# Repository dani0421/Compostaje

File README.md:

# Proyecto de Sistemas embebidos
Este es el repositorio del proyecto (Nombre del proyecto) de la materia de Sitemas embebidos 

## Integrantes
Daniela Valentina Amaya Vargas

Diana Patricia Cortés Nava

Julian David Escobar Jamioy

## Problemática
Cada año la cantidad de residuos organicos a nivel mundial es de 11.200 millones y contribuyen un 5% a las emisiones de gases de efecto invernadero [1], esto cada año incrementa el calentamiento global, sin contar con que poco a poco los basureros alrededor del mundo estan llegando a su maxima capacidad de desechos. La mayoria de estos residuos se generan en los hogares y generalmente no son reutilizados, es por esto que nace la idea de crear (nombre del proyecto), una basurera de desechos organicos capaz de convertir los residuos en compostaje, esto permitirá que se logren reducir las emisiones de gases de efecto invernadero reutilizando los residuos organicos y convirtiendolos en tierra para abonar las plantas del hogar e incluso las plantas de una huerta.

## Objetivos
### Objetivo General:
Desarrollar un sistema embebido que permita darle un manejo óptimo a los desechos organicos de manera cómoda y sencilla, con el fin de poder ser implementado por cualquier usuario de manera doméstica. 
### Objetivos Especificos:
* Diseñar un sistema compacto que integre diseño de PCB, programación de microcontroladores como ESP32 y diseño físico del prototipo.
* Obtener un producto final comercial, en el que se tenga en cuenta también aspectos financieros incluyendo mano de obra.
* Documentar todas las etapas del proceso de creación del proyecto hasta su finalización.

## Alcance
Elaborar un (nombre del proyecto) capaz de transformar, en cada uso, un volumen no mayor a 1.76 L de residuos orgánicos en compostaje. Contará con 3 modos de acuerdo a cuan lleno se encuentre el tambor, los cuales podrán ser elegidos según usuario vea conveniente; una vez elegido un modo, la pantalla OLED indicará la temperatura, humedad y el tiempo que aun haga falta para que el compostaje esté listo y pueda ser retirado de (nombre del proyecto). 

## Requerimientos

### Requerimientos funcionales

* Seleccionar el nivel de compostaje que el dispositivo contiene.
* Visualizar por medio de pantalla el tiempo que falta para finalizar el proceso.
* Notificar al usuario cuando los filtros requieran ser reemplazados. 
* Evitar que el dispositivo genere malos olores.
* Notificar al usuario por medio de un mensaje vía Telegram cuando se acabó el proceso de compostaje.

### Requerimientos no funcionales

* El sistema requiere de un tiempo mínimo de 24 horas para realizar un proceso.

## Diagrama de bloques

## Componentes

### Optoacoplador
Servira para realizar un desacople fisico entre el ESP32 y el controlador (LN298N) de nuestros motores, debido a que su voltaje de trabajo es diferente; se hara uso de la referencia TLP281 de 4 canales.

### Controlador de Motor
Referencia L298N que posee 4 pines de salida, teniendo en cuenta que nuestro motor es un KH56JM2U047 de bifase y con 4 pines de entrada.

### Pantalla OLED
Se usará la referencia SSD1306, la cual posee una matriz de 128x64 y cuya alimentación necesaaria es de 3.3V ([DATASHEET](https://html.alldatasheet.com/html-pdf/1179026/ETC2/SSD1306/701/6/SSD1306.html)); donde el usuario podra observar el tiempo que aun hace falta para que el compostaje este listo. Cuya dirección para I2C es 0x3C.

El SDA se conecta al pin 33 del ESP32 y el SCL al pin 36 de ESP32, cabe resaltar que en la placa no quedaran orificios para la pantalla, unicamente los pines para hacer la conexión.

### Touch
Aunque la ESP posee pines que se pueden usar como touch, se optó por hacer uso de un touch capacitivo externo, el cual nos permitirá abrir la tapa principal, que es por donde se introducira los residuos organicos junto a la tierra que posteriormente se mezclará. La referencia a usar es HW-139

### Motor Nema
Para el proceso de triturado de los residuos organicos y mezclado se usaran dos motores NEMA 17, estos son motores bipolares que pueden ser alimentados con un voltaje de 12 a 24 voltios, se opto por alimentarlos a un voltaje de 12V. 

### Servomotor

El servomotor se usara para abrir y cerrar la tapa de la basuera 

## Diseno PCB
A continuacion se muestra el diseno que se realizo para la PCB

## Montaje fisico
Para el montaje fisico se imprimeron en 3D las siguientes piezas:

Luego se procedio al armado de el prototipo como se muestra en las siguientes imagenes:

https://user-images.githubusercontent.com/92388558/206091587-dc1af1c8-e01d-440c-9be7-15e96c51869d.mp4

## Pruebas de funcionamiento

https://user-images.githubusercontent.com/103794195/206186310-e058958a-483b-43ef-9478-b426c58254a1.mp4

## Referencias
[1] Nations, U. (2022). Datos y cifras | Naciones Unidas. Retrieved 24 August 2022, from https://www.un.org/es/actnow/facts-and-figures

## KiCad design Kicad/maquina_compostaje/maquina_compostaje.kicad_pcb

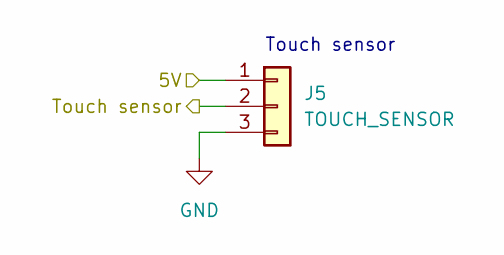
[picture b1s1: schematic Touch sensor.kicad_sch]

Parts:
J5: TOUCH_SENSOR; JST_EH_B3B-EH-A_1x03_P2.50mm_Vertical

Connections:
5V: J5.1; also elsewhere on the board
GND: J5.3; also elsewhere on the board
Touch_sensor: J5.2; also elsewhere on the board

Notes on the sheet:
Touch sensor

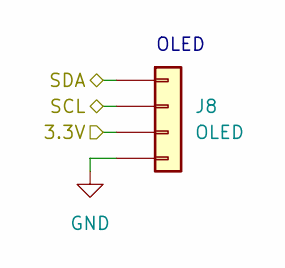
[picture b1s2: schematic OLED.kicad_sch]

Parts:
J8: OLED; JST_EH_B4B-EH-A_1x04_P2.50mm_Vertical

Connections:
3.3V: J8.3; also elsewhere on the board
GND: J8.4; also elsewhere on the board
SCL: J8.2; also elsewhere on the board
SDA: J8.1; also elsewhere on the board

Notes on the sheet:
OLED

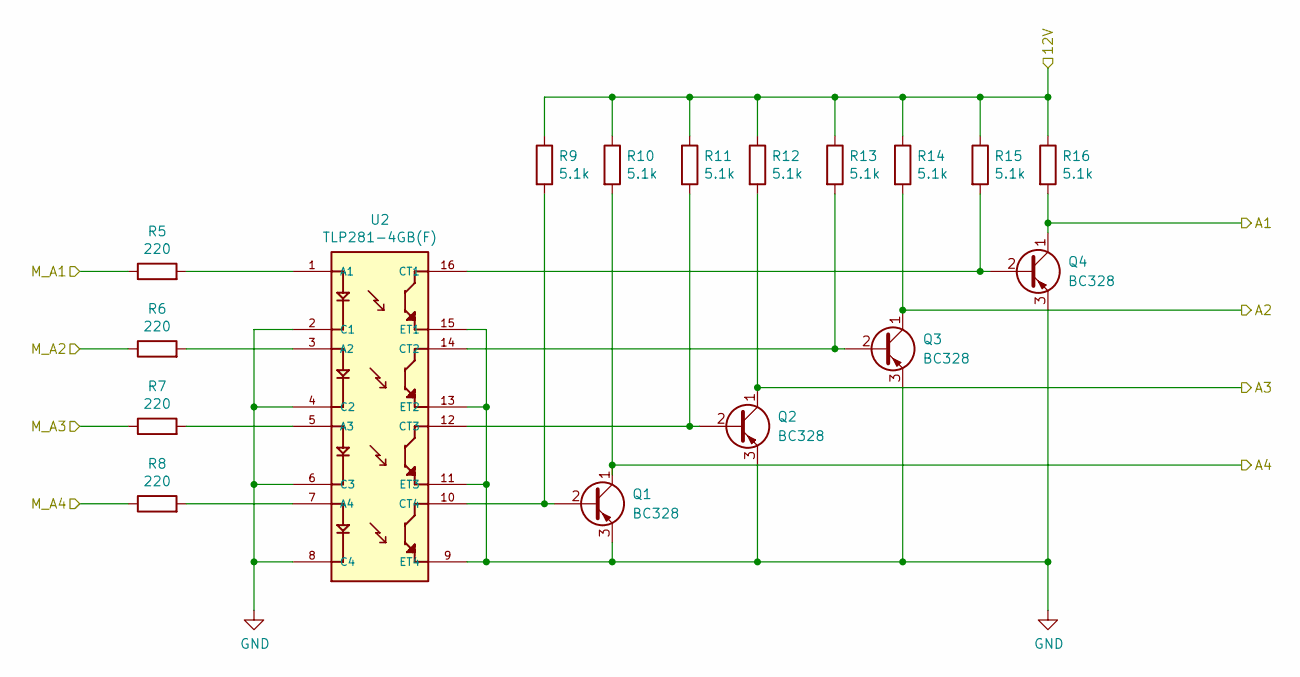
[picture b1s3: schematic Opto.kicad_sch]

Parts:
Q1, Q2, Q3, Q4: BC328; SOT-23
R5, R6, R7, R8: 220; R_1206_3216Metric_Pad1.30x1.75mm_HandSolder
R9, R10, R11, R12, R13, R14, R15, R16: 5.1k; R_1206_3216Metric_Pad1.30x1.75mm_HandSolder
U2: TLP281-4GB(F); SO-16_5.3x10.2mm_P1.27mm

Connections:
12V: R9.1, R10.1, R11.1, R12.1, R13.1, R14.1, R15.1, R16.1; also elsewhere on the board
/Motor A/IN 1A: Q4.1 (C), R16.2; also elsewhere on the board
/Motor A/IN 2A: Q3.1 (C), R14.2; also elsewhere on the board
/Motor A/IN 3A: Q2.1 (C), R12.2; also elsewhere on the board
/Motor A/IN 4A: Q1.1 (C), R10.2; also elsewhere on the board
GND: Q1.3 (E), Q2.3 (E), Q3.3 (E), Q4.3 (E), U2.2 (C1), U2.4 (C2), U2.6 (C3), U2.8 (C4), U2.9 (ET4), U2.11 (ET3), U2.13 (ET2), U2.15 (ET1); also elsewhere on the board
M_A1: R5.1; also elsewhere on the board
M_A2: R6.1; also elsewhere on the board
M_A3: R7.1; also elsewhere on the board
M_A4: R8.1; also elsewhere on the board
unnamed: Q1.2 (B), R9.2, U2.10 (CT4)
unnamed: Q2.2 (B), R11.2, U2.12 (CT3)
unnamed: Q3.2 (B), R13.2, U2.14 (CT2)
unnamed: Q4.2 (B), R15.2, U2.16 (CT1)
unnamed: R5.2, U2.1 (A1)
unnamed: R6.2, U2.3 (A2)
unnamed: R7.2, U2.5 (A3)
unnamed: R8.2, U2.7 (A4)

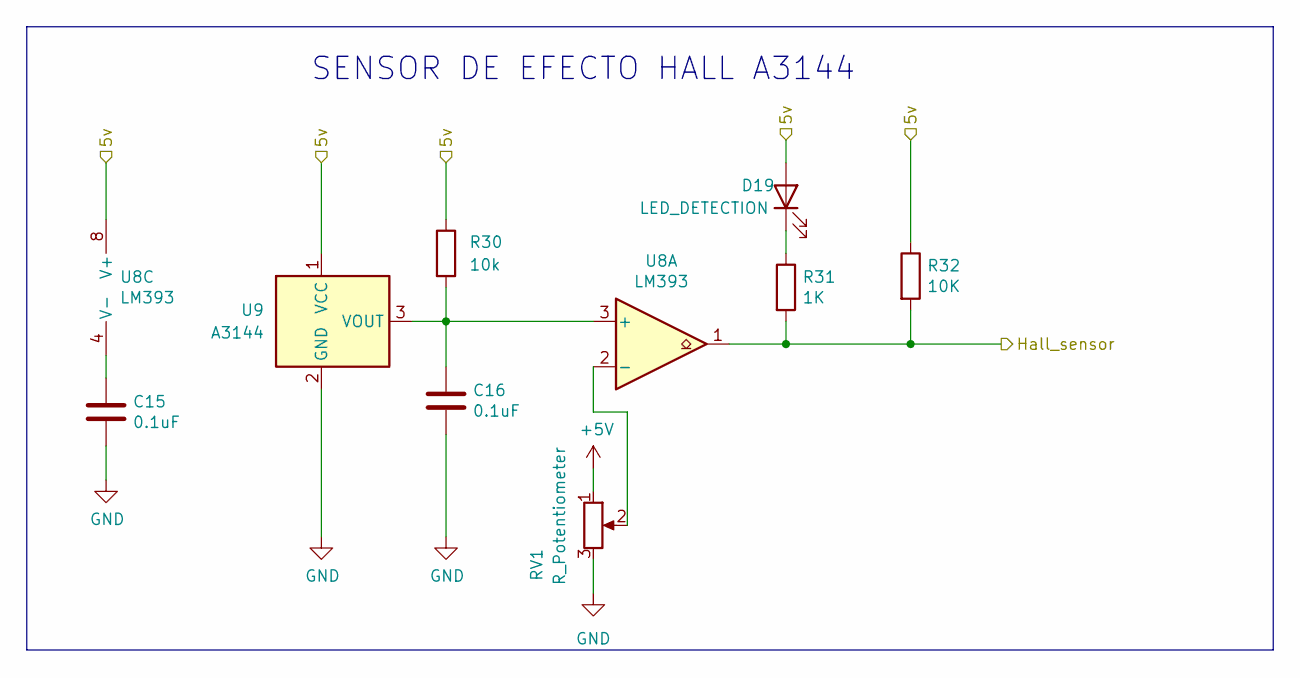
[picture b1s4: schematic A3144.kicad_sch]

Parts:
C15, C16: 0.1uF; C_1206_3216Metric_Pad1.33x1.80mm_HandSolder
D19: LED_DETECTION; LED_1206_3216Metric_Pad1.42x1.75mm_HandSolder
R30: 10k; R_1206_3216Metric_Pad1.30x1.75mm_HandSolder
R31: 1K; R_1206_3216Metric_Pad1.30x1.75mm_HandSolder
R32: 10K; R_1206_3216Metric_Pad1.30x1.75mm_HandSolder
RV1: R_Potentiometer; Potentiometer_ACP_CA6-VSMD_Vertical
U8: LM393; SOIC-8_3.9x4.9mm_P1.27mm
U9: A3144; Allegro_SIP-3

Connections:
5V: D19.2 (A), R30.1, R32.1, RV1.1, U8.8 (V+), U9.1 (VCC); also elsewhere on the board
GND: C15.2, C16.2, RV1.3, U9.2 (GND); also elsewhere on the board
Hall_sensor: R31.2, R32.2, U8.1; also elsewhere on the board
unnamed: C15.1, U8.4 (V-)
unnamed: C16.1, R30.2, U8.3 (+), U9.3 (VOUT)
unnamed: D19.1 (K), R31.1
unnamed: RV1.2, U8.2 (-)

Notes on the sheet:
SENSOR DE EFECTO HALL A3144

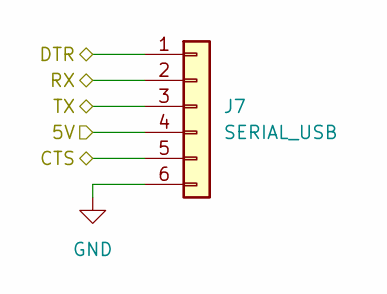
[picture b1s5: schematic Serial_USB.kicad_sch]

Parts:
J7: SERIAL_USB; JST_EH_B6B-EH-A_1x06_P2.50mm_Vertical

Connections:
5V: J7.4; also elsewhere on the board
/Serial_USB/CTS: J7.5
/Serial_USB/DTR: J7.1
GND: J7.6; also elsewhere on the board
RX: J7.2; also elsewhere on the board
TX: J7.3; also elsewhere on the board

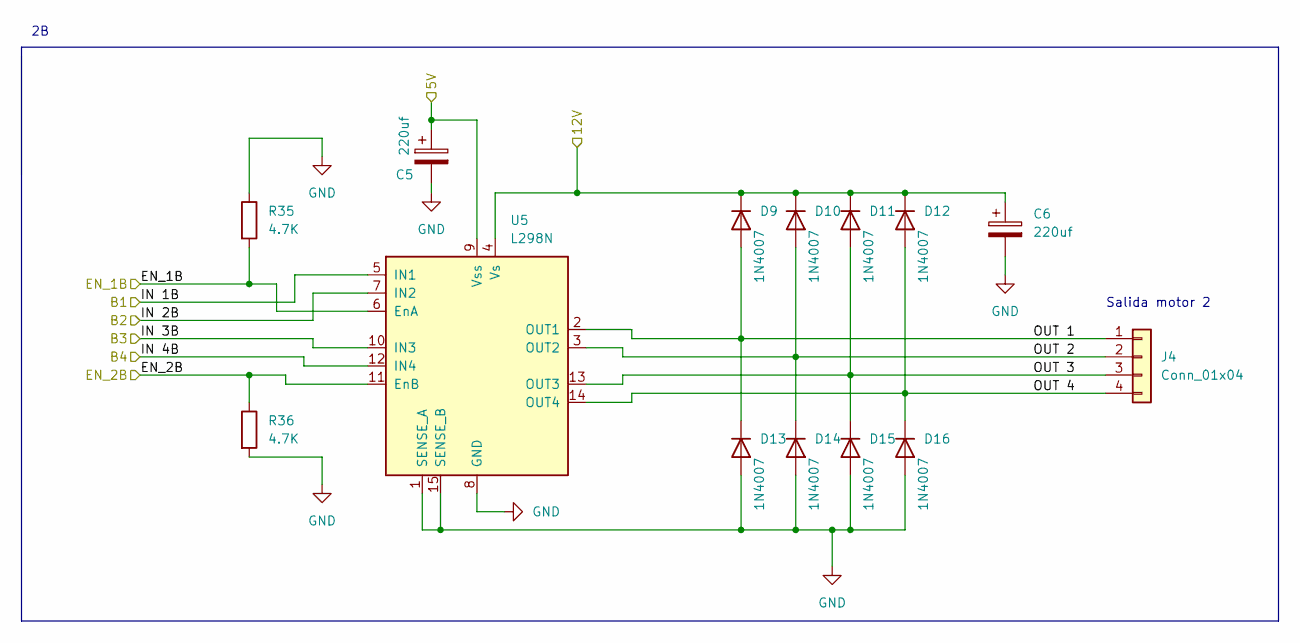
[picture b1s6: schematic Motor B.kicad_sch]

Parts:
C5, C6: 220uf; CP_Elec_8x10
D9, D10, D11, D12, D13, D14, D15, D16: 1N4007; D_SOD-128
J4: Conn_01x04; JST_EH_B4B-EH-A_1x04_P2.50mm_Vertical
R35, R36: 4.7K; R_1206_3216Metric_Pad1.30x1.75mm_HandSolder
U5: L298N; TO-220-15_P2.54x2.54mm_StaggerOdd_Lead4.58mm_Vertical

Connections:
5V: C5.1, U5.9 (Vss); also elsewhere on the board
12V: C6.1, D9.1 (K), D10.1 (K), D11.1 (K), D12.1 (K), U5.4 (Vs); also elsewhere on the board
/Motor B/IN 1B: U5.5 (IN1); also elsewhere on the board
/Motor B/IN 2B: U5.7 (IN2); also elsewhere on the board
/Motor B/IN 3B: U5.10 (IN3); also elsewhere on the board
/Motor B/IN 4B: U5.12 (IN4); also elsewhere on the board
/Motor B/OUT 1: D9.2 (A), D13.1 (K), J4.1, U5.2 (OUT1)
/Motor B/OUT 2: D10.2 (A), D14.1 (K), J4.2, U5.3 (OUT2)
/Motor B/OUT 3: D11.2 (A), D15.1 (K), J4.3, U5.13 (OUT3)
/Motor B/OUT 4: D12.2 (A), D16.1 (K), J4.4, U5.14 (OUT4)
EN_1B: R35.2, U5.6 (EnA); also elsewhere on the board
EN_2B: R36.1, U5.11 (EnB); also elsewhere on the board
GND: C5.2, C6.2, D13.2 (A), D14.2 (A), D15.2 (A), D16.2 (A), R35.1, R36.2, U5.1 (SENSE_A), U5.8 (GND), U5.15 (SENSE_B); also elsewhere on the board

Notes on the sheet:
Salida motor 2

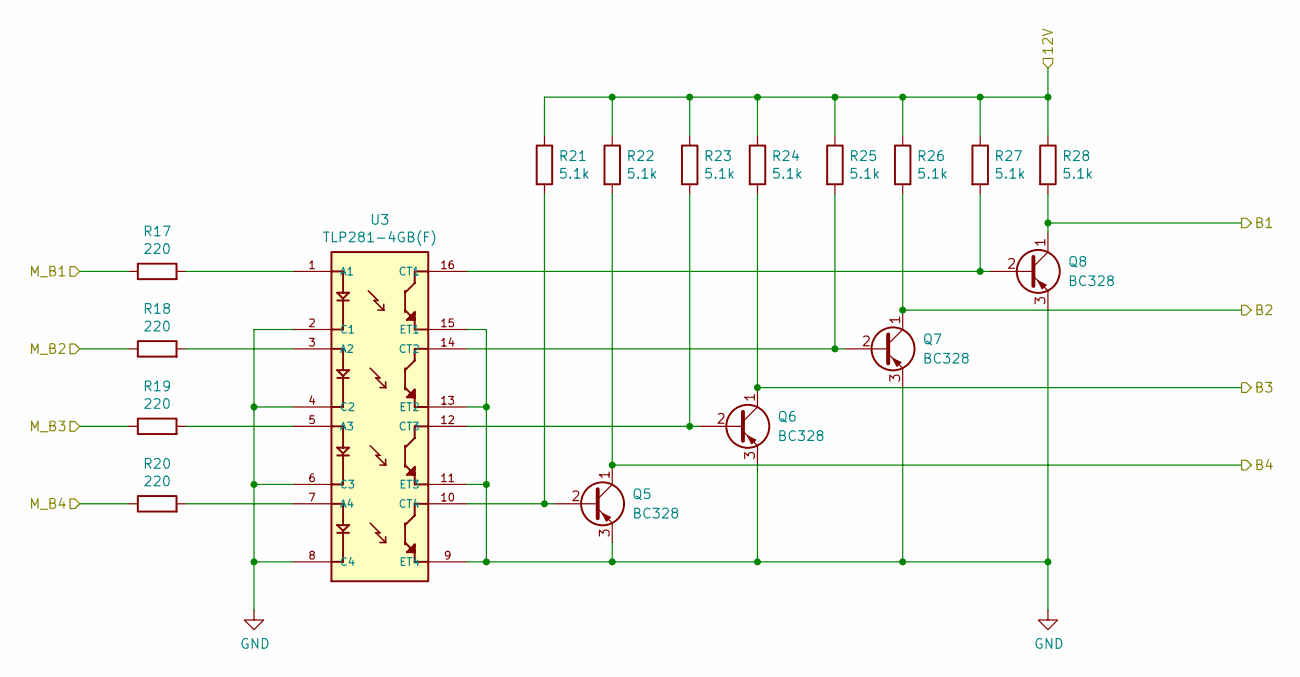
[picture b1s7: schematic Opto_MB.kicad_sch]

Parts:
Q5, Q6, Q7, Q8: BC328; SOT-23
R17, R18, R19, R20: 220; R_1206_3216Metric_Pad1.30x1.75mm_HandSolder
R21, R22, R23, R24, R25, R26, R27, R28: 5.1k; R_1206_3216Metric_Pad1.30x1.75mm_HandSolder
U3: TLP281-4GB(F); SO-16_5.3x10.2mm_P1.27mm

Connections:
12V: R21.1, R22.1, R23.1, R24.1, R25.1, R26.1, R27.1, R28.1; also elsewhere on the board
/Motor B/IN 1B: Q8.1 (C), R28.2; also elsewhere on the board
/Motor B/IN 2B: Q7.1 (C), R26.2; also elsewhere on the board
/Motor B/IN 3B: Q6.1 (C), R24.2; also elsewhere on the board
/Motor B/IN 4B: Q5.1 (C), R22.2; also elsewhere on the board
GND: Q5.3 (E), Q6.3 (E), Q7.3 (E), Q8.3 (E), U3.2 (C1), U3.4 (C2), U3.6 (C3), U3.8 (C4), U3.9 (ET4), U3.11 (ET3), U3.13 (ET2), U3.15 (ET1); also elsewhere on the board
M_B1: R17.1; also elsewhere on the board
M_B2: R18.1; also elsewhere on the board
M_B3: R19.1; also elsewhere on the board
M_B4: R20.1; also elsewhere on the board
unnamed: Q5.2 (B), R21.2, U3.10 (CT4)
unnamed: Q6.2 (B), R23.2, U3.12 (CT3)
unnamed: Q7.2 (B), R25.2, U3.14 (CT2)
unnamed: Q8.2 (B), R27.2, U3.16 (CT1)
unnamed: R17.2, U3.1 (A1)
unnamed: R18.2, U3.3 (A2)
unnamed: R19.2, U3.5 (A3)
unnamed: R20.2, U3.7 (A4)

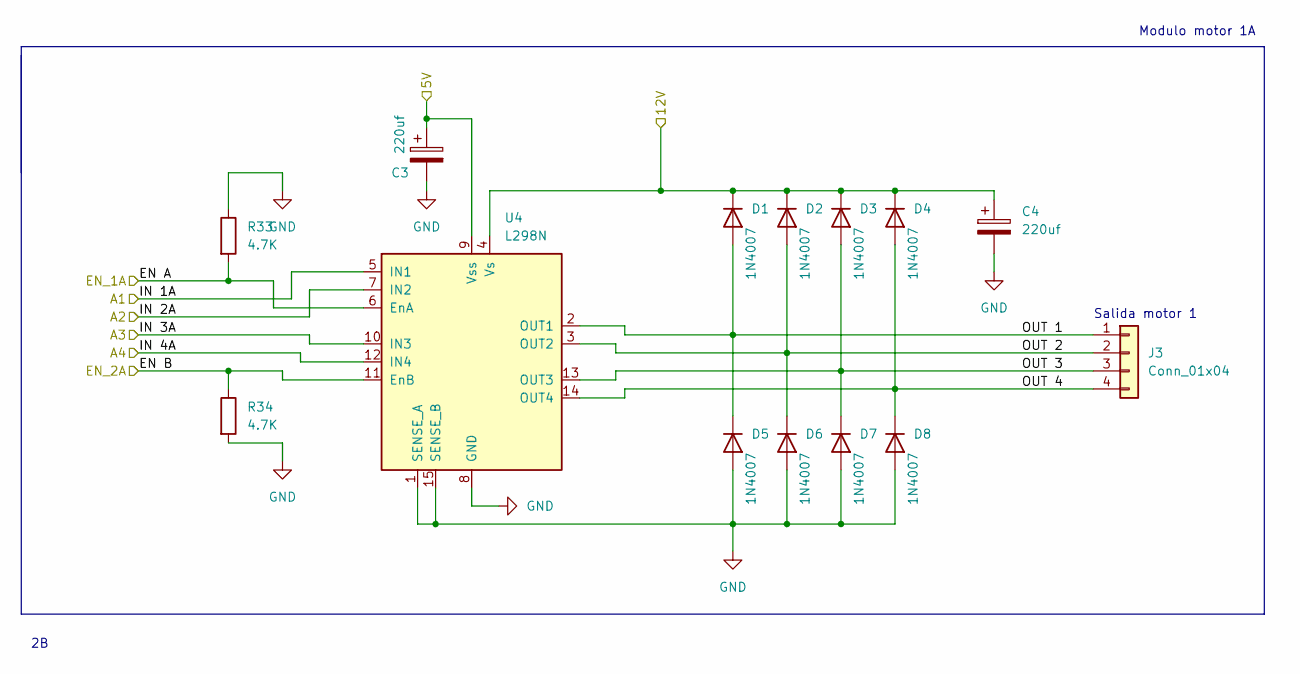
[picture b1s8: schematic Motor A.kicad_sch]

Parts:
C3, C4: 220uf; CP_Elec_8x10
D1, D2, D3, D4, D5, D6, D7, D8: 1N4007; D_SOD-128
J3: Conn_01x04; JST_EH_B4B-EH-A_1x04_P2.50mm_Vertical
R33, R34: 4.7K; R_1206_3216Metric_Pad1.30x1.75mm_HandSolder
U4: L298N; TO-220-15_P2.54x2.54mm_StaggerOdd_Lead4.58mm_Vertical

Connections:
5V: C3.1, U4.9 (Vss); also elsewhere on the board
12V: C4.1, D1.1 (K), D2.1 (K), D3.1 (K), D4.1 (K), U4.4 (Vs); also elsewhere on the board
/Motor A/IN 1A: U4.5 (IN1); also elsewhere on the board
/Motor A/IN 2A: U4.7 (IN2); also elsewhere on the board
/Motor A/IN 3A: U4.10 (IN3); also elsewhere on the board
/Motor A/IN 4A: U4.12 (IN4); also elsewhere on the board
/Motor A/OUT 1: D1.2 (A), D5.1 (K), J3.1, U4.2 (OUT1)
/Motor A/OUT 2: D2.2 (A), D6.1 (K), J3.2, U4.3 (OUT2)
/Motor A/OUT 3: D3.2 (A), D7.1 (K), J3.3, U4.13 (OUT3)
/Motor A/OUT 4: D4.2 (A), D8.1 (K), J3.4, U4.14 (OUT4)
EN_1A: R33.2, U4.6 (EnA); also elsewhere on the board
EN_2A: R34.1, U4.11 (EnB); also elsewhere on the board
GND: C3.2, C4.2, D5.2 (A), D6.2 (A), D7.2 (A), D8.2 (A), R33.1, R34.2, U4.1 (SENSE_A), U4.8 (GND), U4.15 (SENSE_B); also elsewhere on the board

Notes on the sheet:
Modulo motor 1A
Salida motor 1

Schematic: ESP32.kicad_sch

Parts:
C1: 10uf; C_1206_3216Metric_Pad1.33x1.80mm_HandSolder
C2: 10uf; C_1206_3216Metric
C17: 0.1uF; C_1206_3216Metric_Pad1.33x1.80mm_HandSolder
C18: 10uF; C_1206_3216Metric_Pad1.33x1.80mm_HandSolder
J1: OTHERS; JST_EH_B6B-EH-A_1x06_P2.50mm_Vertical
J2: GPIO; JST_EH_B5B-EH-A_1x05_P2.50mm_Vertical
R1, R4: 10k; R_1206_3216Metric_Pad1.30x1.75mm_HandSolder
R2, R3: 4.7K; R_1206_3216Metric_Pad1.30x1.75mm_HandSolder
SW1: RESET; smd_push2
SW2: BOOT; smd_push2
U1: ESP32-WROOM-32

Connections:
3.3V: C17.2, C18.1, R1.1, R4.1, U1.2 (VDD); also elsewhere on the board
+3.3V: R2.2, R3.2
/ESP32/SCK: J1.2, U1.20 (SCK/CLK)
/ESP32/SCS: J1.1, U1.19 (SCS/CMD)
/ESP32/SD0: J1.6, U1.21 (SDO/SD0)
/ESP32/SD1: J1.5, U1.22 (SDI/SD1)
/ESP32/SD2: J1.4, U1.17 (SHD/SD2)
/ESP32/SD3: J1.3, U1.18 (SWP/SD3)
/ESP32/gpio2: J2.1, U1.24 (IO2)
/ESP32/gpio16: J2.2, U1.27 (IO16)
/ESP32/gpio17: J2.3, U1.28 (IO17)
/ESP32/gpio23: J2.4, U1.37 (IO23)
/ESP32/gpio35: J2.5, U1.7 (IO35)
EN_1A: U1.26 (IO4); also elsewhere on the board
EN_1B: U1.9 (IO33); also elsewhere on the board
EN_2A: U1.29 (IO5); also elsewhere on the board
EN_2B: U1.6 (IO34); also elsewhere on the board
GND: C1.2, C2.2, C17.1, C18.2, SW1.1, SW1.2, SW2.1, SW2.2, U1.1 (GND), U1.15 (GND), U1.38 (GND), U1.39 (GND); also elsewhere on the board
Hall_sensor: U1.31 (IO19); also elsewhere on the board
M_A1: U1.14 (IO12); also elsewhere on the board
M_A2: U1.16 (IO13); also elsewhere on the board
M_A3: U1.13 (IO14); also elsewhere on the board
M_A4: U1.23 (IO15); also elsewhere on the board
M_B1: U1.10 (IO25); also elsewhere on the board
M_B2: U1.11 (IO26); also elsewhere on the board
M_B3: U1.12 (IO27); also elsewhere on the board
M_B4: U1.8 (IO32); also elsewhere on the board
unnamed: C1.1, R1.2, SW1.3, SW1.4, U1.3 (EN)
unnamed: C2.1, R4.2, SW2.3, SW2.4, U1.25 (IO0)
RX: U1.35 (TXD0/IO1); also elsewhere on the board
SCL: R2.1, U1.36 (IO22); also elsewhere on the board
SDA: R3.1, U1.33 (IO21); also elsewhere on the board
TX: U1.34 (RXD0/IO3); also elsewhere on the board
Touch_sensor: U1.30 (IO18); also elsewhere on the board

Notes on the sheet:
gpio MA 12,13,14,15 MB 25,26,27,32 para motores SDA y SCL van a OLED gpio18 touch sensor gpio19 sensor de efecto hall

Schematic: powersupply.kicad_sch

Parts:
C7, C10, C11, C14: 10uf; C_1206_3216Metric_Pad1.33x1.80mm_HandSolder
C8, C12: 10uf; CP_Elec_6.3x5.4
C9, C13: 100nf; C_1206_3216Metric_Pad1.33x1.80mm_HandSolder
D17: 1N4002; D_SOD-128
D18: LED; LED_1206_3216Metric_Pad1.42x1.75mm_HandSolder
F1: 1A; Fuse_1206_3216Metric_Pad1.42x1.75mm_HandSolder
F2: 2A; Fuse_1206_3216Metric_Pad1.42x1.75mm_HandSolder
J6: Barrel_Jack_MountingPin; BarrelJack_Horizontal
R29: 1k; R_1206_3216Metric_Pad1.30x1.75mm_HandSolder
U6: AMS1117-5.0; SOT-223; PARTREV N/A
U7: AMS1117-3.3; SOT-223; PARTREV NA

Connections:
3.3V: C12.1, C13.1, C14.1, U7.2 (VOUT); also elsewhere on the board
5V: C8.1, C9.1, C10.1, C11.1, D18.2 (A), U6.2 (VOUT), U7.3 (VIN); also elsewhere on the board
12V: F2.2; also elsewhere on the board
GND: C7.2, C8.2, C9.2, C10.2, C11.2, C12.2, C13.2, C14.2, J6.2, J6.MP (MountPin), R29.2, U6.1 (GND/ADJ), U7.1 (ADJ/GND); also elsewhere on the board
unnamed: C7.1, F1.2, U6.3 (VIN)
unnamed: D17.1 (K), F1.1, F2.1
unnamed: D17.2 (A), J6.1
unnamed: D18.1 (K), R29.1

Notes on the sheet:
Led de energizacion
Regulador de 5V - 1A
Regulador de 3.3V - 1A

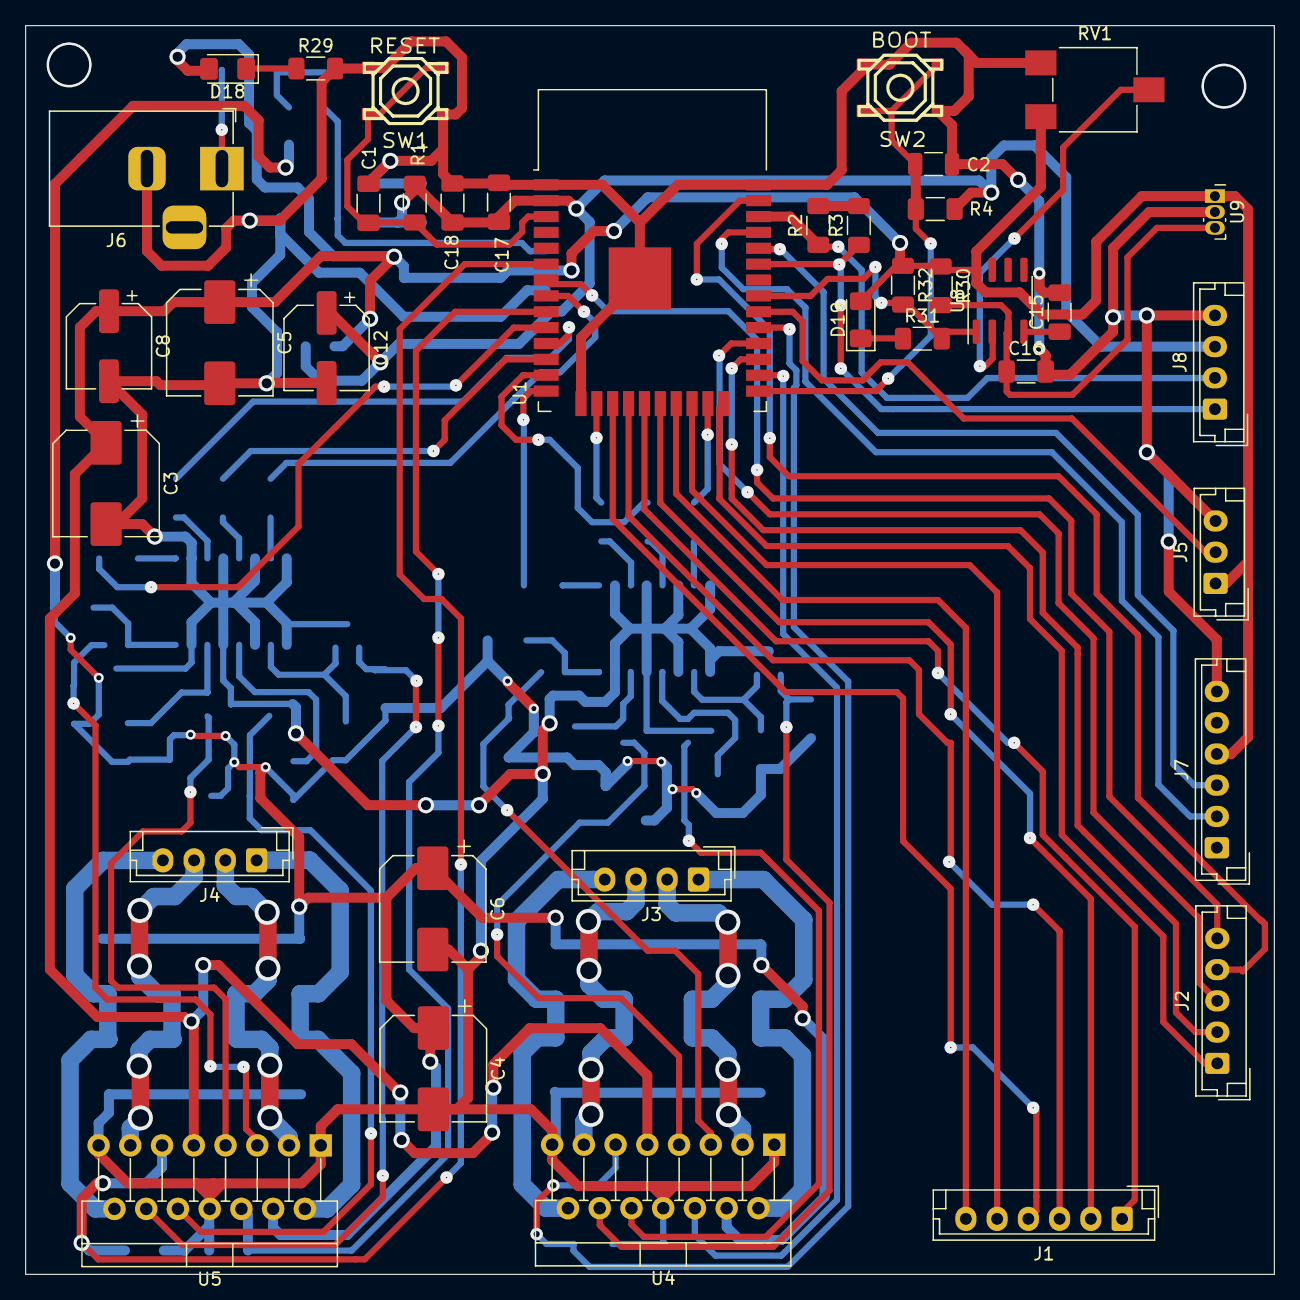
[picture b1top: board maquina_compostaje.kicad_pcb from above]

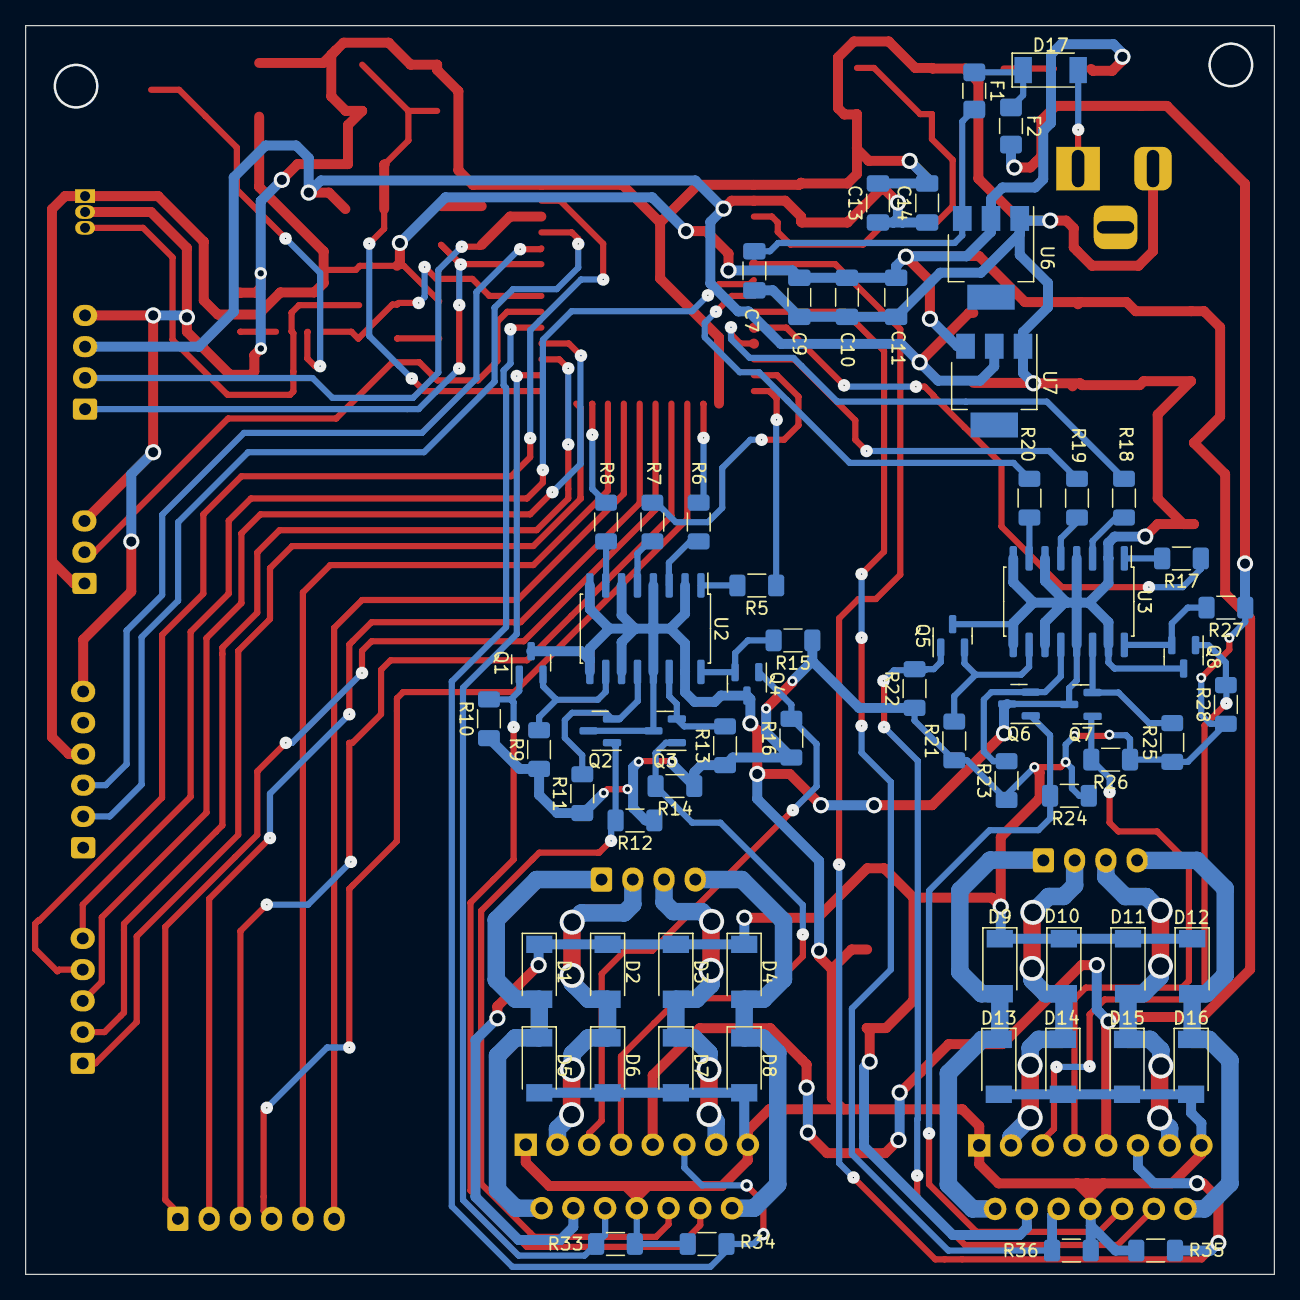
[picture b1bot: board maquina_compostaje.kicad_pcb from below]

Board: 2 copper layers, 99.9 x 99.9 mm, 103 parts (65 on the bottom side), 76 nets.

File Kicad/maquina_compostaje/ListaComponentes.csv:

"Id";"Designator";"Package";"Quantity";"Designation";"Supplier and ref";
1;"C18";"C_1206_3216Metric_Pad1.33x1.80mm_HandSolder";1;"10uF";;;
2;"SW2";"smd_push2";1;"BOOT";;;
3;"C17,C15,C16";"C_1206_3216Metric_Pad1.33x1.80mm_HandSolder";3;"0.1uF";;;
4;"R3,R2,R36,R34,R35,R33";"R_1206_3216Metric_Pad1.30x1.75mm_HandSolder";6;"4.7K";;;
5;"C4,C5,C6,C3";"CP_Elec_8x10";4;"220uf";;;
6;"J2";"JST_EH_B5B-EH-A_1x05_P2.50mm_Vertical";1;"GPIO";;;
7;"SW1";"smd_push2";1;"RESET";;;
8;"J5";"JST_EH_B3B-EH-A_1x03_P2.50mm_Vertical";1;"TOUCH_SENSOR";;;
9;"R4,R30,R1";"R_1206_3216Metric_Pad1.30x1.75mm_HandSolder";3;"10k";;;
10;"D18";"LED_1206_3216Metric_Pad1.42x1.75mm_HandSolder";1;"LED";;;
11;"U9";"Allegro_SIP-3";1;"A3144";;;
12;"RV1";"Potentiometer_ACP_CA6-VSMD_Vertical";1;"R_Potentiometer";;;
13;"J8";"JST_EH_B4B-EH-A_1x04_P2.50mm_Vertical";1;"OLED";;;
14;"U8";"SOIC-8_3.9x4.9mm_P1.27mm";1;"LM393";;;
15;"U5,U4";"TO-220-15_P2.54x2.54mm_StaggerOdd_Lead4.58mm_Vertical";2;"L298N";;;
16;"C2";"C_1206_3216Metric";1;"10uf";;;
17;"R32";"R_1206_3216Metric_Pad1.30x1.75mm_HandSolder";1;"10K";;;
18;"U1";"ESP32-WROOM-32";1;"ESP32-WROOM-32";;;
19;"D19";"LED_1206_3216Metric_Pad1.42x1.75mm_HandSolder";1;"LED_DETECTION";;;
20;"J7";"JST_EH_B6B-EH-A_1x06_P2.50mm_Vertical";1;"SERIAL_USB";;;
21;"C8,C12";"CP_Elec_6.3x5.4";2;"10uf";;;
22;"J1";"JST_EH_B6B-EH-A_1x06_P2.50mm_Vertical";1;"OTHERS";;;
23;"J3,J4";"JST_EH_B4B-EH-A_1x04_P2.50mm_Vertical";2;"Conn_01x04";;;
24;"R31";"R_1206_3216Metric_Pad1.30x1.75mm_HandSolder";1;"1K";;;
25;"J6";"BarrelJack_Horizontal";1;"Barrel_Jack_MountingPin";;;
26;"C1,C11,C14,C10,C7";"C_1206_3216Metric_Pad1.33x1.80mm_HandSolder";5;"10uf";;;
27;"R29";"R_1206_3216Metric_Pad1.30x1.75mm_HandSolder";1;"1k";;;
28;"R14,R16,R23,R22,R9,R21,R28,R15,R13,R25,R26,R24,R11,R12,R10,R27";"R_1206_3216Metric_Pad1.30x1.75mm_HandSolder";16;"5.1k";;;
29;"D8,D1,D7,D6,D13,D11,D14,D4,D10,D15,D3,D16,D5,D12,D9,D2";"D_SOD-128";16;"1N4007";;;
30;"Q7,Q6,Q8,Q2,Q3,Q1,Q4,Q5";"SOT-23";8;"BC328";;;
31;"R18,R8,R20,R19,R5,R17,R7,R6";"R_1206_3216Metric_Pad1.30x1.75mm_HandSolder";8;"220";;;
32;"C13,C9";"C_1206_3216Metric_Pad1.33x1.80mm_HandSolder";2;"100nf";;;
33;"U3,U2";"SO-16_5.3x10.2mm_P1.27mm";2;"TLP281-4GB(F)";;;
34;"U7";"SOT-223";1;"AMS1117-3.3";;;
35;"F2";"Fuse_1206_3216Metric_Pad1.42x1.75mm_HandSolder";1;"2A";;;
36;"D17";"D_SOD-128";1;"1N4002";;;
37;"U6";"SOT-223";1;"AMS1117-5.0";;;
38;"F1";"Fuse_1206_3216Metric_Pad1.42x1.75mm_HandSolder";1;"1A";;;

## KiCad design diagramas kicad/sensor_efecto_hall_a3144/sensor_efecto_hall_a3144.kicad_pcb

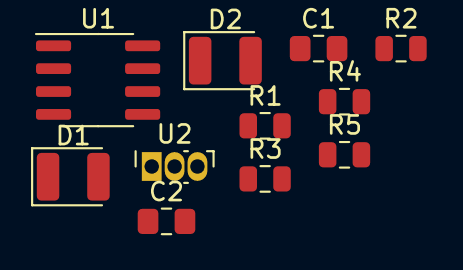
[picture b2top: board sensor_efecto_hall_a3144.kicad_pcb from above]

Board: 2 copper layers, 11 parts (0 on the bottom side), 8 nets, no tracks yet.

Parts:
C1, C2: 0.1uF; C_0805_2012Metric_Pad1.15x1.40mm_HandSolder
D1: LED_DETECTION; LED_1210_3225Metric
D2: LED; LED_1210_3225Metric
R1, R2, R4: 10K; R_0805_2012Metric
R3, R5: 1K; R_0805_2012Metric
U1: LM393; SOIC-8_3.9x4.9mm_P1.27mm
U2: A3144; Allegro_SIP-3

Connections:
+5V: D1.2, R1.1, R4.1, R5.1, U1.8, U2.1
GND: C1.2, C2.2, D2.1, R2.2
unnamed: C1.1, U1.4
unnamed: C2.1, R1.2, U1.3, U2.2
unnamed: D1.1, R3.1
unnamed: D2.2, R5.2
unnamed: R2.1, U1.2
unnamed: R3.2, R4.2, U1.1

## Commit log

2022-09-12 creación carpeta de diagramas en Kicad
2022-09-12 creación del diagrama esquematico del sensor A3144
2022-09-13 Create Esquematico Driver A4988
2022-10-02 Create Optoacoplador
2022-10-02 Optoacoplador
2022-10-02 Create opto
2022-10-06 Create Diseno Kicad
2022-10-06 Diseno Kicad
2022-10-11 inicio del ruteo
2022-10-13 se agregaron componentes en la parte inferior de la placa
2022-10-15 PCB ACTUALIZADA
2022-10-17 Lista de materiales
2022-12-07 Espero que funcione
2022-12-07 Create Código
2022-12-07 Create ,
2022-12-07 Intento 3
